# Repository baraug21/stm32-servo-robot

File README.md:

# Servo-Driven Robot (WIP)

> **Project Status: Work in Progress**
> This project is currently under active development as a team project. 
> Hardware design (schematics and PCB layout) is completed, while the firmware implementation (motor drivers and user interface) is currently being written.

## Overview
A custom robotic platform featuring servo motor control (PWM) and a matrix keypad interface...

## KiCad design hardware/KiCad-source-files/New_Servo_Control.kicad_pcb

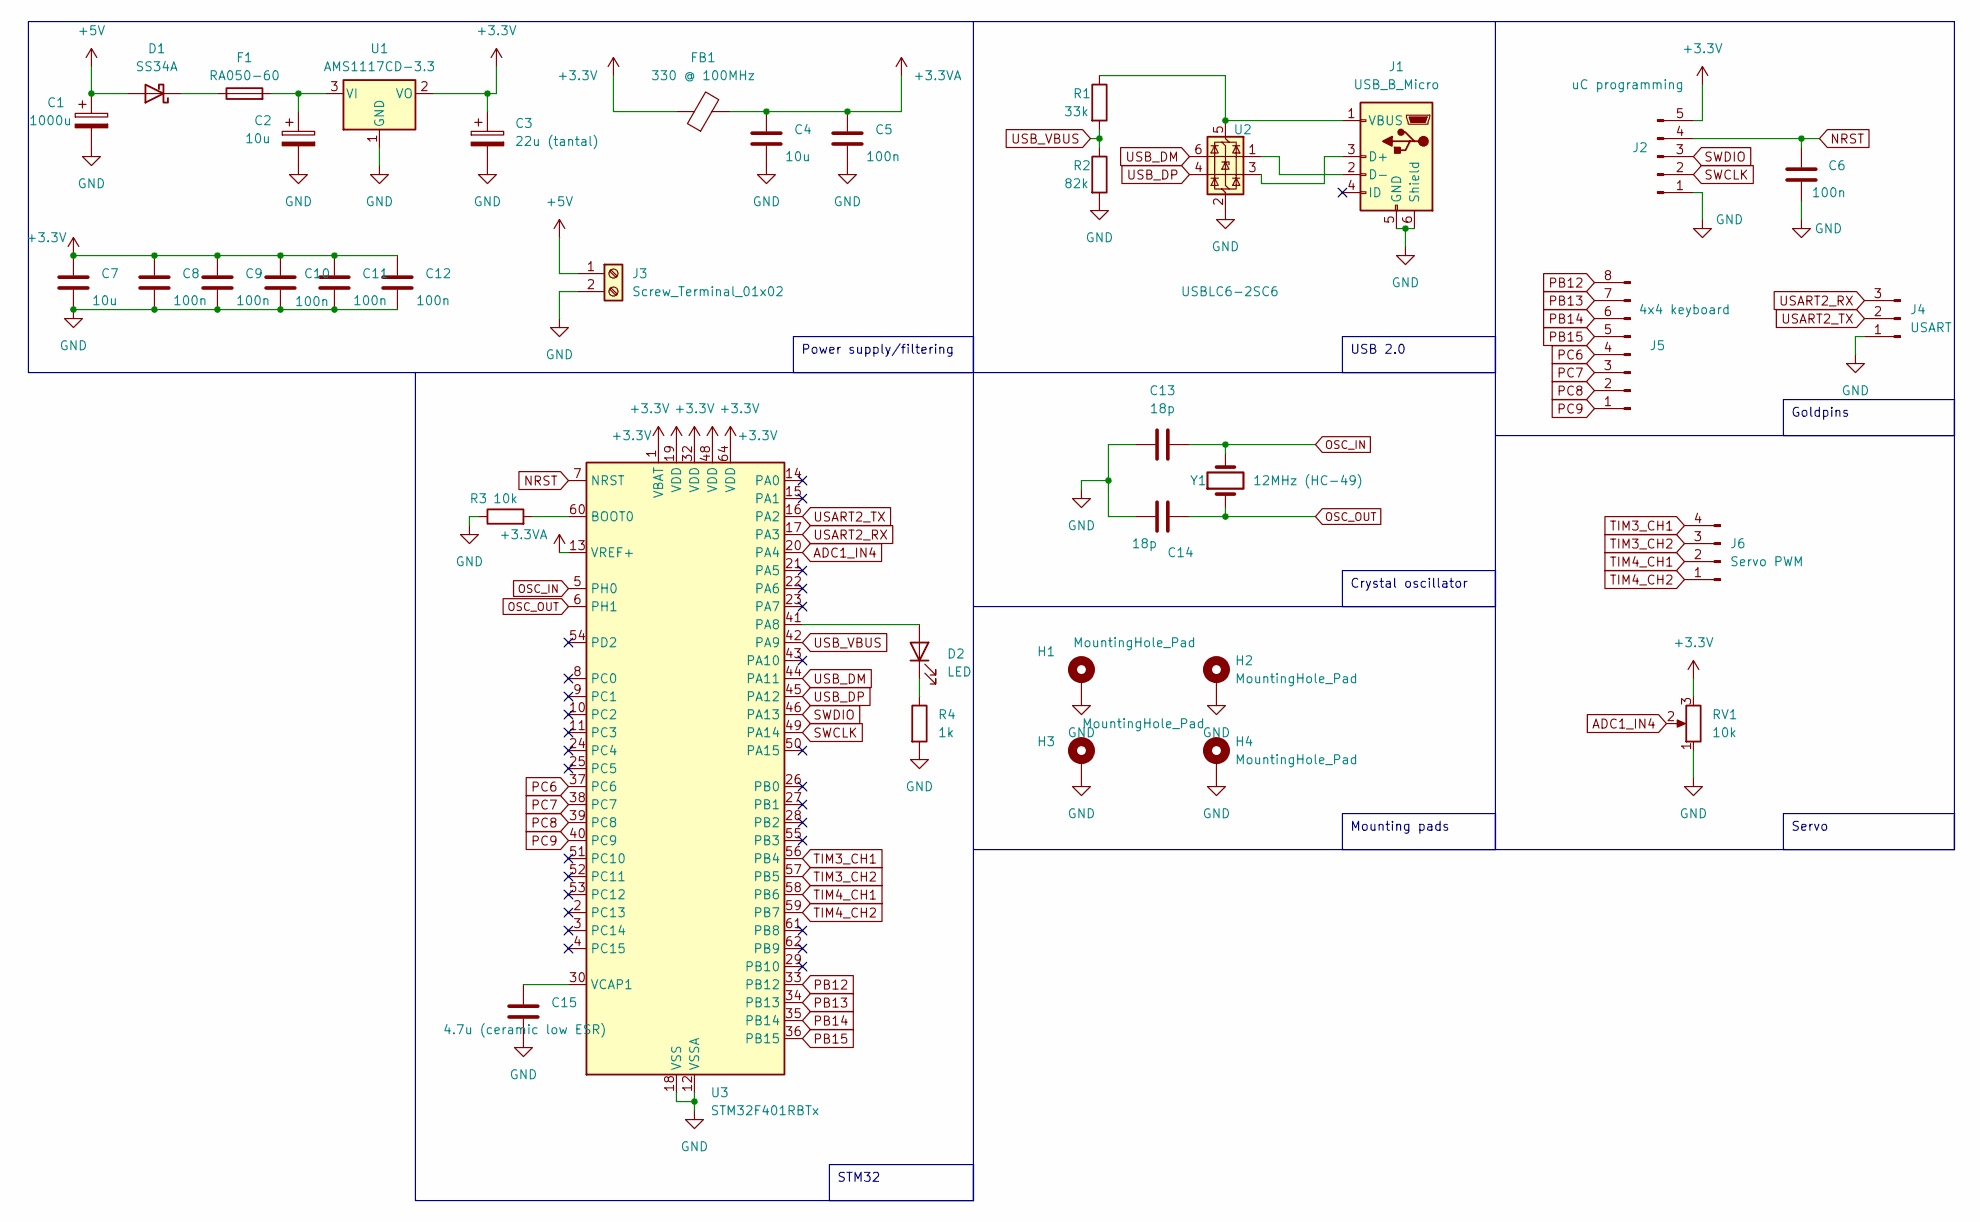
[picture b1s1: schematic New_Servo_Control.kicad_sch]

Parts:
C1: 1000u; CP_Radial_D10.0mm_P5.00mm
C2: 10u; CP_Radial_D8.0mm_P5.00mm
C3: 22u (tantal); CP_EIA-3528-12_Kemet-T_Pad1.50x2.35mm_HandSolder
C4, C7: 10u; C_0805_2012Metric_Pad1.18x1.45mm_HandSolder
C5, C6, C8, C9, C10, C11, C12: 100n; C_0805_2012Metric_Pad1.18x1.45mm_HandSolder
C13, C14: 18p; C_0805_2012Metric_Pad1.18x1.45mm_HandSolder
C15: 4.7u (ceramic low ESR); C_0805_2012Metric_Pad1.18x1.45mm_HandSolder
D1: SS34A; D_SMA_Handsoldering
D2: LED; LED_0603_1608Metric_Pad1.05x0.95mm_HandSolder
F1: RA050-60; Fuse_BelFuse_0ZRE0025FF_L9.6mm_W3.8mm
FB1: 330 @ 100MHz; R_0805_2012Metric_Pad1.20x1.40mm_HandSolder
H1, H2, H3, H4: MountingHole_Pad; MountingHole_3.2mm_M3_Pad_Via
J1: USB_B_Micro; USB_Micro-B_Molex_47346-0001
J2: uC programming; PinHeader_1x05_P2.54mm_Vertical
J3: Screw_Terminal_01x02; TerminalBlock_RND_205-00045_1x02_P5.00mm_Horizontal
J4: USART; PinHeader_1x03_P2.54mm_Vertical
J5: 4x4 keyboard; PinHeader_1x08_P2.54mm_Vertical
J6: Servo PWM; PinHeader_1x04_P2.54mm_Vertical
R1: 33k; R_0805_2012Metric_Pad1.20x1.40mm_HandSolder
R2: 82k; R_0805_2012Metric_Pad1.20x1.40mm_HandSolder
R3: 10k; R_0805_2012Metric_Pad1.20x1.40mm_HandSolder
R4: 1k; R_0805_2012Metric_Pad1.20x1.40mm_HandSolder
RV1: 10k; Potentiometer_Piher_PT-6-H_Horizontal
U1: AMS1117CD-3.3; SOT-223-3_TabPin2
U2: USBLC6-2SC6; SOT-23-6
U3: STM32F401RBTx; LQFP-64_10x10mm_P0.5mm
Y1: 12MHz (HC-49); Crystal_HC49-U_Vertical

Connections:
+3.3V: C3.1, C7.1, C8.1, C9.1, C10.1, C11.1, C12.1, FB1.1, J2.5, RV1.3, U1.2 (VO), U3.1 (VBAT), U3.19 (VDD), U3.32 (VDD), U3.48 (VDD), U3.64 (VDD)
+3.3VA: C4.1, C5.1, FB1.2, U3.13 (VREF+)
+5V: C1.1, D1.2 (A), J3.1
ADC1_IN4: RV1.2, U3.20 (PA4)
GND: C1.2, C2.2, C3.2, C4.2, C5.2, C6.2, C7.2, C8.2, C9.2, C10.2, C11.2, C12.2, C13.1, C14.1, C15.1, H1.1, H2.1, H3.1, H4.1, J1.5 (GND), J1.6 (Shield), J2.1, J3.2, J4.1, R2.2, R3.1, R4.2, RV1.1, U1.1 (GND), U2.2 (GND), U3.12 (VSSA), U3.18 (VSS), U3.31 (VSS), U3.47 (VSS), U3.63 (VSS)
NRST: C6.1, J2.4, U3.7 (NRST)
unnamed: D1.1 (K), F1.1
unnamed: D2.2 (A), U3.41 (PA8)
unnamed: D2.1 (K), R4.1
unnamed: J1.3 (D+), U2.3 (I/O2)
unnamed: J1.2 (D-), U2.1 (I/O1)
unnamed: J1.1 (VBUS), R1.1, U2.5 (VBUS)
unnamed: C2.1, F1.2, U1.3 (VI)
unnamed: R3.2, U3.60 (BOOT0)
unnamed: C15.2, U3.30 (VCAP1)
OSC_IN: C13.2, U3.5 (PH0), Y1.2
OSC_OUT: C14.2, U3.6 (PH1), Y1.1
PB12: J5.8, U3.33 (PB12)
PB13: J5.7, U3.34 (PB13)
PB14: J5.6, U3.35 (PB14)
PB15: J5.5, U3.36 (PB15)
PC6: J5.4, U3.37 (PC6)
PC7: J5.3, U3.38 (PC7)
PC8: J5.2, U3.39 (PC8)
PC9: J5.1, U3.40 (PC9)
SWCLK: J2.2, U3.49 (PA14)
SWDIO: J2.3, U3.46 (PA13)
TIM3_CH1: J6.4, U3.56 (PB4)
TIM3_CH2: J6.3, U3.57 (PB5)
TIM4_CH1: J6.2, U3.58 (PB6)
TIM4_CH2: J6.1, U3.59 (PB7)
USART2_RX: J4.3, U3.17 (PA3)
USART2_TX: J4.2, U3.16 (PA2)
USB_DM: U2.6 (I/O1), U3.44 (PA11)
USB_DP: U2.4 (I/O2), U3.45 (PA12)
USB_VBUS: R1.2, R2.1, U3.42 (PA9)

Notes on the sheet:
Mounting pads
Power supply/filtering
Crystal oscillator
USB 2.0
STM32
Goldpins
Servo

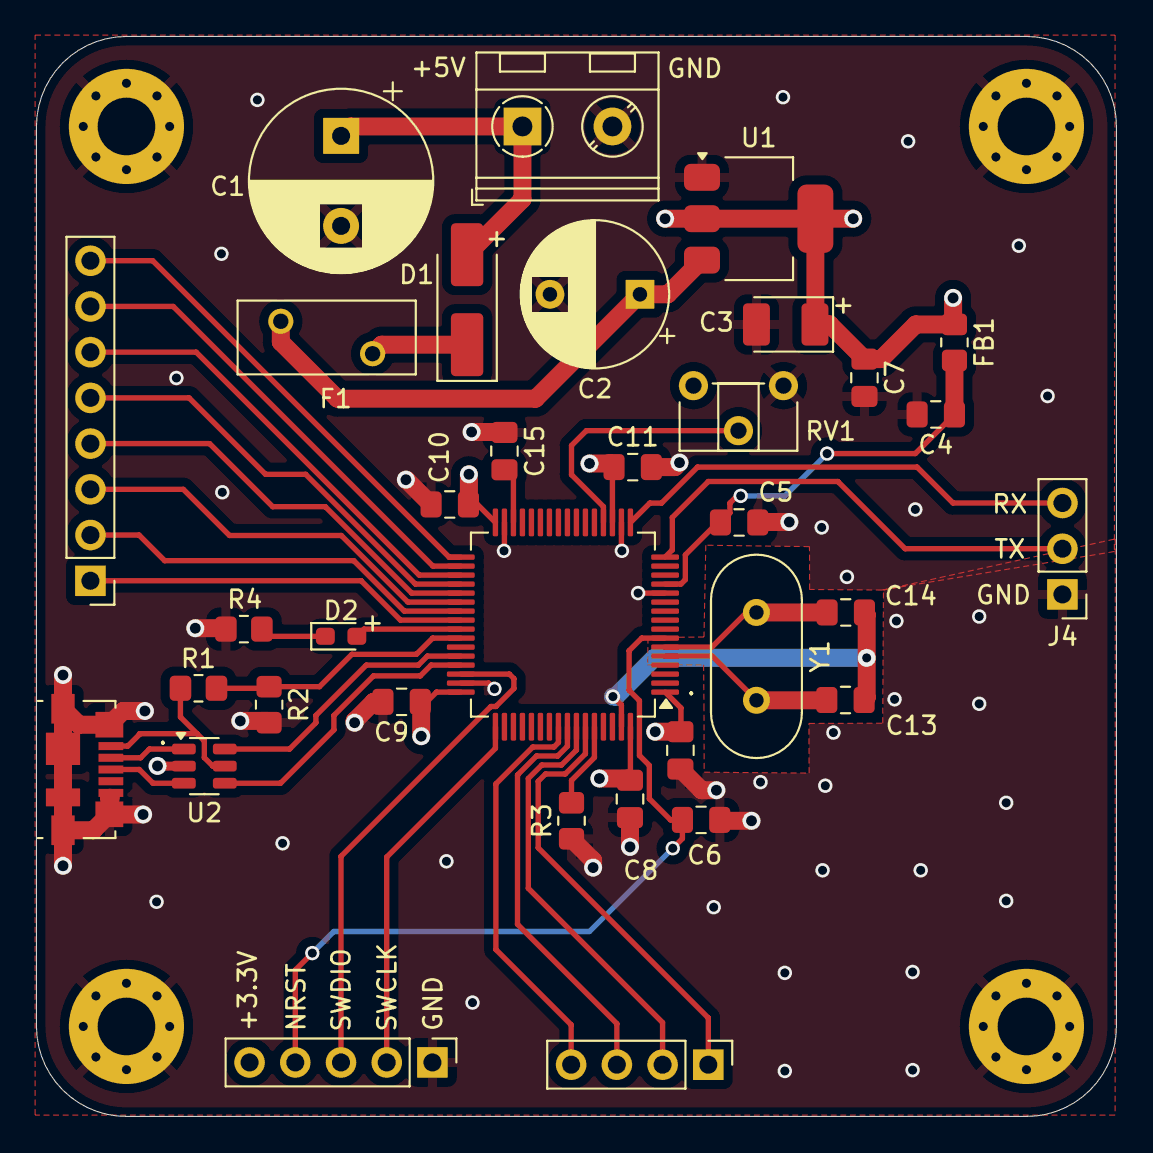
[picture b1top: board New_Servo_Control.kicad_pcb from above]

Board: 4 copper layers, 60.0 x 60.0 mm, 38 parts (0 on the bottom side), 36 nets.
